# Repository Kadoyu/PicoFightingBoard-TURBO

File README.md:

# Pico Fighting Board TURBO
Forked from [FeralAI/PicoFightingBoard](https://github.com/FeralAI/PicoFightingBoard)

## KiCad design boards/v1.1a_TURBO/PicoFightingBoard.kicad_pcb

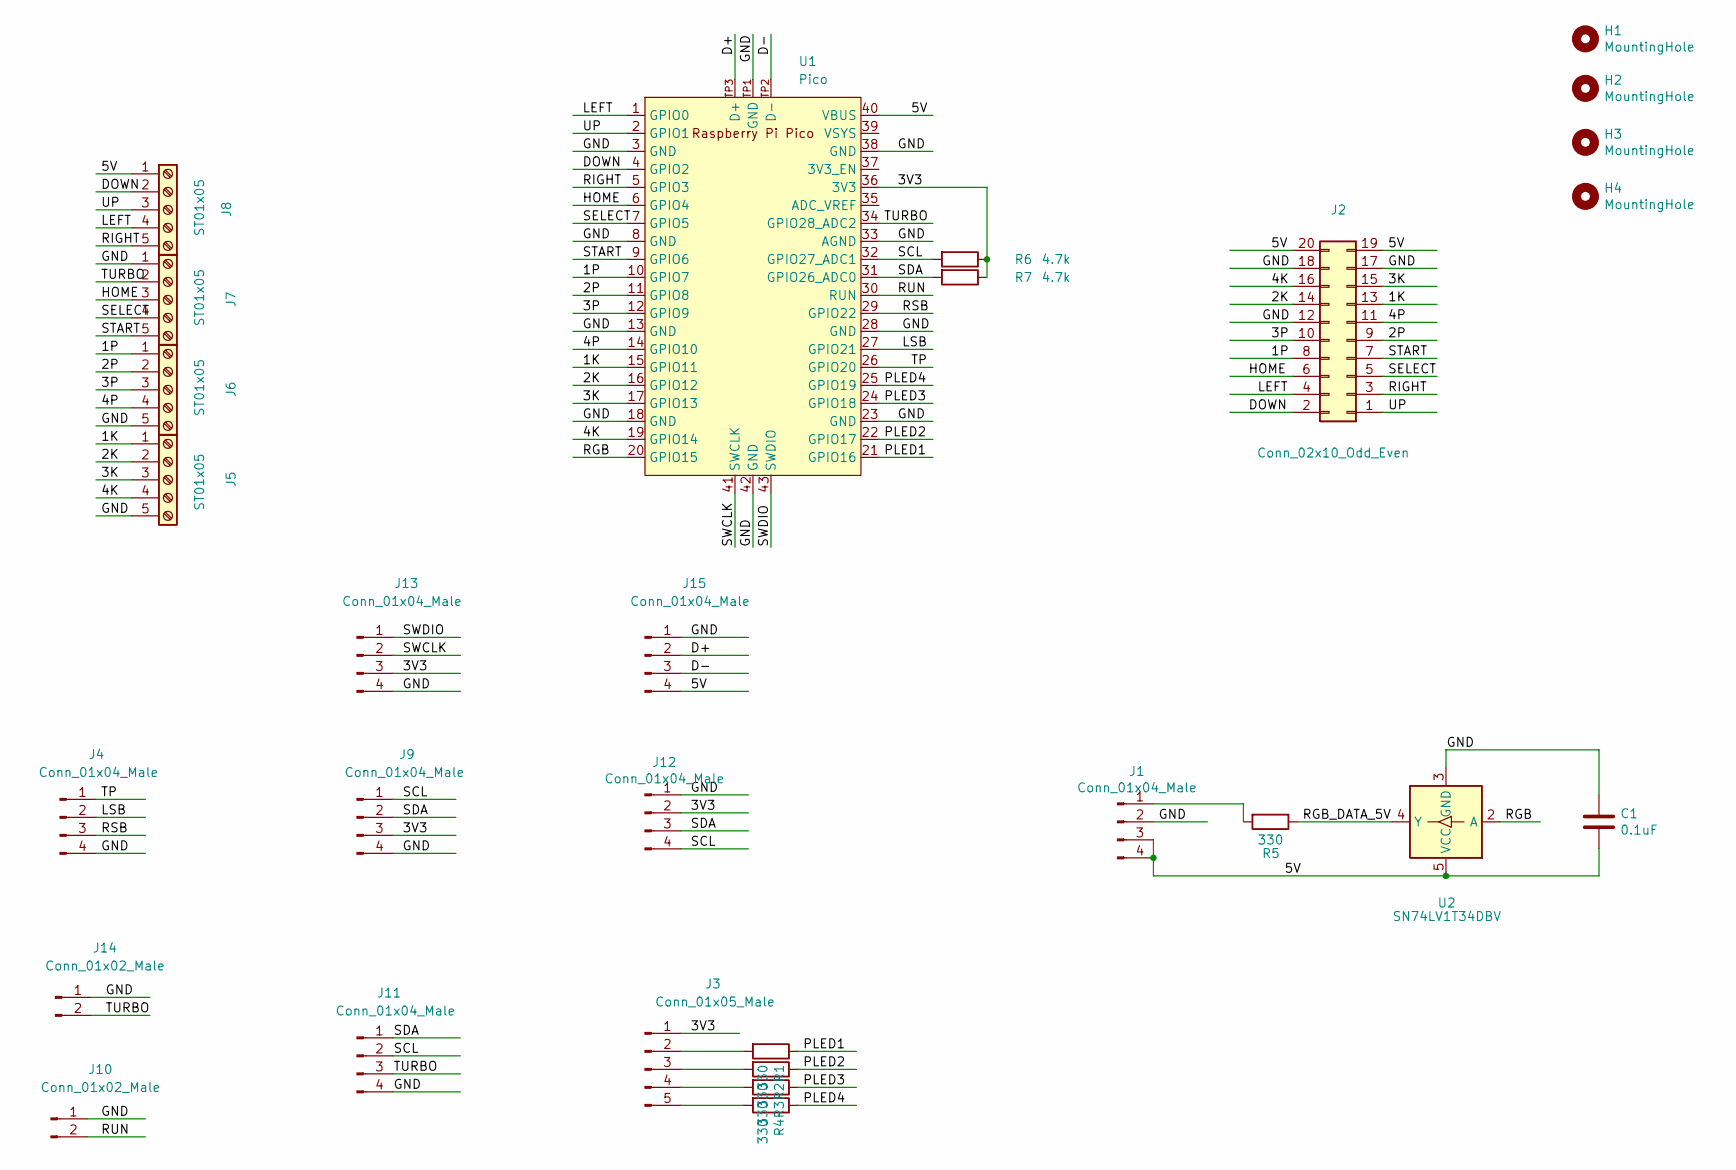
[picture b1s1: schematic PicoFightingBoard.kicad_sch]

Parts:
C1: 0.1uF; C_0805_2012Metric
H1, H2, H3, H4: MountingHole; MountingHole_3.5mm
J1, J4, J11, J12: Conn_01x04_Male; JST_PH_B4B-PH-K_1x04_P2.00mm_Vertical
J2: Conn_02x10_Odd_Even; PinHeader_2x10_P2.54mm_Vertical
J3: Conn_01x05_Male; JST_PH_B5B-PH-K_1x05_P2.00mm_Vertical
J5, J6, J7, J8: ST01x05; TerminalBlock_MetzConnect_Type059_RT06305HBWC_1x05_P3.50mm_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
J9, J13: Conn_01x04_Male; BOOM_SH_C145961_1x04_P1.00mm_Vertical
J10, J14: Conn_01x02_Male; PinHeader_1x02_P2.54mm_Vertical
J15: Conn_01x04_Male; PinHeader_1x04_P2.54mm_Vertical
R1, R2, R3, R4, R5: 330; R_0805_2012Metric
R6, R7: 4.7k; R_0805_2012Metric
U1: Pico; RPi_Pico_SMD_TH_TP
U2: SN74LV1T34DBV; SOT-23-5

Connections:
/1K: J2.13, J5.1, U1.15 (GPIO11)
/1P: J2.8, J6.1, U1.10 (GPIO7)
/2K: J2.14, J5.2, U1.16 (GPIO12)
/2P: J2.9, J6.2, U1.11 (GPIO8)
/3K: J2.15, J5.3, U1.17 (GPIO13)
/3P: J2.10, J6.3, U1.12 (GPIO9)
/3V3: J3.1, J9.3, J12.2, J13.3, R6.1, R7.1, U1.36 (3V3)
/4K: J2.16, J5.4, U1.19 (GPIO14)
/4P: J2.11, J6.4, U1.14 (GPIO10)
/5V: C1.2, J1.3, J1.4, J2.19, J2.20, J8.1, J15.4, U1.40 (VBUS), U2.5 (VCC)
/D+: J15.2, U1.TP3 (D+)
/D-: J15.3, U1.TP2 (D-)
/DOWN: J2.2, J8.2, U1.4 (GPIO2)
/GND: C1.1, J1.2, J2.12, J2.17, J2.18, J4.4, J5.5, J6.5, J7.1, J9.4, J10.1, J11.4, J12.1, J13.4, J14.1, J15.1, U1.3 (GND), U1.8 (GND), U1.13 (GND), U1.18 (GND), U1.23 (GND), U1.28 (GND), U1.33 (AGND), U1.38 (GND), U1.42 (GND), U1.TP1 (GND), U2.3 (GND)
/HOME: J2.6, J7.3, U1.6 (GPIO4)
/LEFT: J2.4, J8.4, U1.1 (GPIO0)
/LSB: J4.2, U1.27 (GPIO21)
/PLED1: R1.1, U1.21 (GPIO16)
/PLED2: R2.1, U1.22 (GPIO17)
/PLED3: R3.1, U1.24 (GPIO18)
/PLED4: R4.1, U1.25 (GPIO19)
/RGB: U1.20 (GPIO15), U2.2 (A)
/RGB_DATA_5V: R5.1, U2.4 (Y)
/RIGHT: J2.3, J8.5, U1.5 (GPIO3)
/RSB: J4.3, U1.29 (GPIO22)
/RUN: J10.2, U1.30 (RUN)
/SCL: J9.1, J11.2, J12.4, R6.2, U1.32 (GPIO27_ADC1)
/SDA: J9.2, J11.1, J12.3, R7.2, U1.31 (GPIO26_ADC0)
/SELECT: J2.5, J7.4, U1.7 (GPIO5)
/START: J2.7, J7.5, U1.9 (GPIO6)
/SWCLK: J13.2, U1.41 (SWCLK)
/SWDIO: J13.1, U1.43 (SWDIO)
/TP: J4.1, U1.26 (GPIO20)
/TURBO: J7.2, J11.3, J14.2, U1.34 (GPIO28_ADC2)
/UP: J2.1, J8.3, U1.2 (GPIO1)
unnamed: J1.1, R5.2
unnamed: J3.2, R1.2
unnamed: J3.3, R2.2
unnamed: J3.4, R3.2
unnamed: J3.5, R4.2

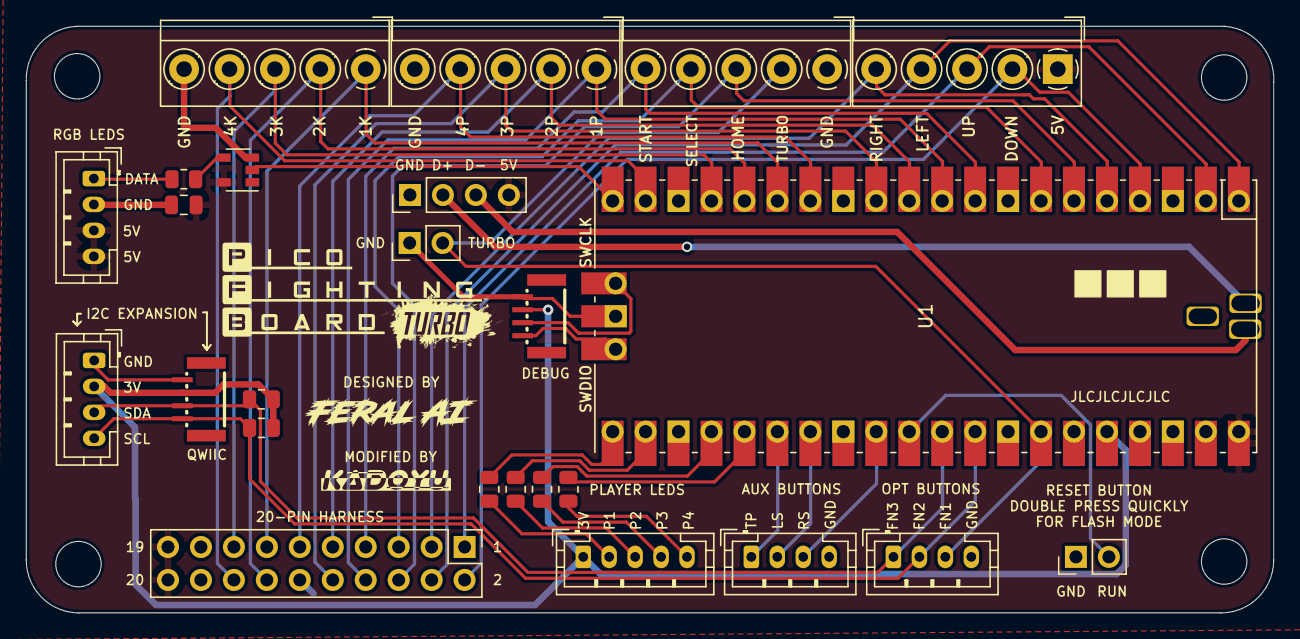
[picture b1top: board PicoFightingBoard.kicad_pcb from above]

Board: 2 copper layers, 96.1 x 45.2 mm, 29 parts (0 on the bottom side), 40 nets.

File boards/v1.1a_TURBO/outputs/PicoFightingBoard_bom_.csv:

Component,Description,Part,References,Value,Footprint,Quantity Per PCB,Datasheet
1,Unpolarized capacitor,C,C1,0.1uF,C_0805_2012Metric,1,~
2,"Generic connector, single row, 01x02, script generated (kicad-library-utils/schlib/autogen/connector/)",Conn_01x02_Male,J10 J14,Conn_01x02_Male,PinHeader_1x02_P2.54mm_Vertical,2,~
3,"Generic connector, single row, 01x04, script generated (kicad-library-utils/schlib/autogen/connector/)",Conn_01x04_Male,J1 J4 J11 J12,Conn_01x04_Male,JST_PH_B4B-PH-K_1x04_P2.00mm_Vertical,4,~
4,"Generic connector, single row, 01x04, script generated (kicad-library-utils/schlib/autogen/connector/)",Conn_01x04_Male,J9 J13,Conn_01x04_Male,BOOM_SH_C145961_1x04_P1.00mm_Vertical,2,~
5,"Generic connector, single row, 01x04, script generated (kicad-library-utils/schlib/autogen/connector/)",Conn_01x04_Male,J15,Conn_01x04_Male,PinHeader_1x04_P2.54mm_Vertical,1,~
6,"Generic connector, single row, 01x05, script generated (kicad-library-utils/schlib/autogen/connector/)",Conn_01x05_Male,J3,Conn_01x05_Male,JST_PH_B5B-PH-K_1x05_P2.00mm_Vertical,1,~
7,"Generic connector, double row, 02x10, odd/even pin numbering scheme (row 1 odd numbers, row 2 even numbers), script generated (kicad-library-utils/schlib/autogen/connector/)",Conn_02x10_Odd_Even,J2,Conn_02x10_Odd_Even,PinHeader_2x10_P2.54mm_Vertical,1,~
8,"Generic screw terminal, single row, 01x05, script generated (kicad-library-utils/schlib/autogen/connector/)",Screw_Terminal_01x05,J5 J6 J7 J8,ST01x05,TerminalBlock_MetzConnect_Type059_RT06305HBWC_1x05_P3.50mm_Horizontal,4,~
9,Resistor,R,R1 R2 R3 R4 R5,330,R_0805_2012Metric,5,~
10,Resistor,R,R6 R7,4.7k,R_0805_2012Metric,2,~
11,,Pico_tp,U1,Pico,RPi_Pico_SMD_TH_TP,1,
12,"Single Power Supply, Single Buffer GATE, CMOS Logic, Level Shifter, SOT-23-5",SN74LV1T34DBV,U2,SN74LV1T34DBV,SOT-23-5,1,https://www.ti.com/lit/ds/symlink/sn74lv1t34.pdf





Component Groups:,12
Component Count:,25
Fitted Components:,25
Number of PCBs:,1
Total components:,25
Schematic Version:,
Schematic Date:,
PCB Variant:,default
BoM Date:,2023/02/09 11:54:59
Schematic Source:,PicoFightingBoard.kicad_sch
KiCad Version:,Eeschema (6.0.11)

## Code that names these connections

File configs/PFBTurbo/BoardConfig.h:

/*
 * SPDX-License-Identifier: MIT
 * SPDX-FileCopyrightText: Copyright (c) 2024 OpenStickCommunity (gp2040-ce.info)
 */

#ifndef PICO_BOARD_CONFIG_H_
#define PICO_BOARD_CONFIG_H_

#include "enums.pb.h"
#include "class/hid/hid.h"

#define BOARD_CONFIG_LABEL "Pico Fighting Board"

// Main pin mapping Configuration
//                                                  // GP2040 | Xinput | Switch  | PS3/4/5  | Dinput | Arcade |
#define GPIO_PIN_01 GpioAction::BUTTON_PRESS_UP     // UP     | UP     | UP      | UP       | UP     | UP     |
#define GPIO_PIN_02 GpioAction::BUTTON_PRESS_DOWN   // DOWN   | DOWN   | DOWN    | DOWN     | DOWN   | DOWN   |
#define GPIO_PIN_03 GpioAction::BUTTON_PRESS_RIGHT  // RIGHT  | RIGHT  | RIGHT   | RIGHT    | RIGHT  | RIGHT  |
#define GPIO_PIN_00 GpioAction::BUTTON_PRESS_LEFT   // LEFT   | LEFT   | LEFT    | LEFT     | LEFT   | LEFT   |
#define GPIO_PIN_11 GpioAction::BUTTON_PRESS_B1     // B1     | A      | B       | Cross    | 2      | K1     |
#define GPIO_PIN_12 GpioAction::BUTTON_PRESS_B2     // B2     | B      | A       | Circle   | 3      | K2     |
#define GPIO_PIN_13 GpioAction::BUTTON_PRESS_R2     // R2     | RT     | ZR      | R2       | 8      | K3     |
#define GPIO_PIN_14 GpioAction::BUTTON_PRESS_L2     // L2     | LT     | ZL      | L2       | 7      | K4     |
#define GPIO_PIN_07 GpioAction::BUTTON_PRESS_B3     // B3     | X      | Y       | Square   | 1      | P1     |
#define GPIO_PIN_08 GpioAction::BUTTON_PRESS_B4     // B4     | Y      | X       | Triangle | 4      | P2     |
#define GPIO_PIN_09 GpioAction::BUTTON_PRESS_R1     // R1     | RB     | R       | R1       | 6      | P3     |
#define GPIO_PIN_10 GpioAction::BUTTON_PRESS_L1     // L1     | LB     | L       | L1       | 5      | P4     |
#define GPIO_PIN_05 GpioAction::BUTTON_PRESS_S1     // S1     | Back   | Minus   | Select   | 9      | Coin   |
#define GPIO_PIN_06 GpioAction::BUTTON_PRESS_S2     // S2     | Start  | Plus    | Start    | 10     | Start  |
#define GPIO_PIN_21 GpioAction::BUTTON_PRESS_L3     // L3     | LS     | LS      | L3       | 11     | LS     |
#define GPIO_PIN_22 GpioAction::BUTTON_PRESS_R3     // R3     | RS     | RS      | R3       | 12     | RS     |
#define GPIO_PIN_04 GpioAction::BUTTON_PRESS_A1     // A1     | Guide  | Home    | PS       | 13     | ~      |
#define GPIO_PIN_20 GpioAction::BUTTON_PRESS_A2     // A2     | ~      | Capture | ~        | 14     | ~      |

// Setting GPIO pins to assigned by add-on
//
#define GPIO_PIN_15 GpioAction::ASSIGNED_TO_ADDON
#define GPIO_PIN_16 GpioAction::ASSIGNED_TO_ADDON
#define GPIO_PIN_17 GpioAction::ASSIGNED_TO_ADDON
#define GPIO_PIN_18 GpioAction::ASSIGNED_TO_ADDON
#define GPIO_PIN_19 GpioAction::ASSIGNED_TO_ADDON
#define GPIO_PIN_26 GpioAction::ASSIGNED_TO_ADDON
#define GPIO_PIN_27 GpioAction::ASSIGNED_TO_ADDON

#define TURBO_ENABLED 1
#define GPIO_PIN_28 GpioAction::BUTTON_PRESS_TURBO

// Keyboard Mapping Configuration
//                                            // GP2040 | Xinput | Switch  | PS3/4/5  | Dinput | Arcade |
#define KEY_DPAD_UP     HID_KEY_ARROW_UP      // UP     | UP     | UP      | UP       | UP     | UP     |
#define KEY_DPAD_DOWN   HID_KEY_ARROW_DOWN    // DOWN   | DOWN   | DOWN    | DOWN     | DOWN   | DOWN   |
#define KEY_DPAD_RIGHT  HID_KEY_ARROW_RIGHT   // RIGHT  | RIGHT  | RIGHT   | RIGHT    | RIGHT  | RIGHT  |
#define KEY_DPAD_LEFT   HID_KEY_ARROW_LEFT    // LEFT   | LEFT   | LEFT    | LEFT     | LEFT   | LEFT   |
#define KEY_BUTTON_B1   HID_KEY_SHIFT_LEFT    // B1     | A      | B       | Cross    | 2      | K1     |
#define KEY_BUTTON_B2   HID_KEY_Z             // B2     | B      | A       | Circle   | 3      | K2     |
#define KEY_BUTTON_R2   HID_KEY_X             // R2     | RT     | ZR      | R2       | 8      | K3     |
#define KEY_BUTTON_L2   HID_KEY_V             // L2     | LT     | ZL      | L2       | 7      | K4     |
#define KEY_BUTTON_B3   HID_KEY_CONTROL_LEFT  // B3     | X      | Y       | Square   | 1      | P1     |
#define KEY_BUTTON_B4   HID_KEY_ALT_LEFT      // B4     | Y      | X       | Triangle | 4      | P2     |
#define KEY_BUTTON_R1   HID_KEY_SPACE         // R1     | RB     | R       | R1       | 6      | P3     |
#define KEY_BUTTON_L1   HID_KEY_C             // L1     | LB     | L       | L1       | 5      | P4     |
#define KEY_BUTTON_S1   HID_KEY_5             // S1     | Back   | Minus   | Select   | 9      | Coin   |
#define KEY_BUTTON_S2   HID_KEY_1             // S2     | Start  | Plus    | Start    | 10     | Start  |
#define KEY_BUTTON_L3   HID_KEY_EQUAL         // L3     | LS     | LS      | L3       | 11     | LS     |
#define KEY_BUTTON_R3   HID_KEY_MINUS         // R3     | RS     | RS      | R3       | 12     | RS     |
#define KEY_BUTTON_A1   HID_KEY_9             // A1     | Guide  | Home    | PS       | 13     | ~      |
#define KEY_BUTTON_A2   HID_KEY_F2            // A2     | ~      | Capture | ~        | 14     | ~      |
#define KEY_BUTTON_FN   -1                    // Hotkey Function                                        |

#define BOARD_LEDS_PIN 15

#define LED_BRIGHTNESS_MAXIMUM 150
#define LEDS_PER_PIXEL 2

#define LEDS_DPAD_LEFT   11
#define LEDS_DPAD_DOWN   10
#define LEDS_DPAD_RIGHT  9
#define LEDS_DPAD_UP     0
#define LEDS_BUTTON_B3   8
#define LEDS_BUTTON_B4   7
#define LEDS_BUTTON_R1   6
#define LEDS_BUTTON_L1   5
#define LEDS_BUTTON_B1   1
#define LEDS_BUTTON_B2   2
#define LEDS_BUTTON_R2   3
#define LEDS_BUTTON_L2   4
#define LEDS_BUTTON_S1   -1
#define LEDS_BUTTON_S2   -1
#define LEDS_BUTTON_L3   -1
#define LEDS_BUTTON_R3   -1
#define LEDS_BUTTON_A1   -1
#define LEDS_BUTTON_A2   -1

#define PLED_TYPE PLED_TYPE_PWM
#define PLED1_PIN 16
#define PLED2_PIN 17
#define PLED3_PIN 18
#define PLED4_PIN 19

#define HAS_I2C_DISPLAY 1
#define I2C1_ENABLED 1
#define I2C1_PIN_SDA 26
#define I2C1_PIN_SCL 27
#define DISPLAY_I2C_BLOCK i2c1


#define BUTTON_LAYOUT BUTTON_LAYOUT_STICKLESS
#define BUTTON_LAYOUT_RIGHT BUTTON_LAYOUT_STICKLESSB

#endif

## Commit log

2023-02-08 add readme & editorconfig
2023-02-08 add README.md
2023-02-28 add config file
2023-03-04 add KiCad files
2024-08-23 Update BoardConfig.h
    Update for latest firmware
